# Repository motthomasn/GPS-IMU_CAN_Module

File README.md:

# GPS-IMU_CAN_Module
Teensy 3.2 based controller board designed to collect GPS &amp; IMU data from SkyTraq Venus838LPx and Bosch BNO055 breakout boards and transmit the data via CAN-Bus

This module was built for my CBR250RRi project. The aim was to have a standalone GPS & IMU module which could send high frequency positional data via CAN-Bus to an ECU or datalogger and therefore improve track performance analysis.

The SkyTraq Venus838LPx breakout board allows GPS data acquisition rates up to 50Hz. The BNO055 breakout board was chosen due to the fact that spatial orientation data was calculated internally. However, the spatial orientation (Euler) angles have proved unreliable so a different sensor or calculation method may need to be looked at.

For further details on the CBR250RRi project, refer to the website https://www.cbr250rri.com/.

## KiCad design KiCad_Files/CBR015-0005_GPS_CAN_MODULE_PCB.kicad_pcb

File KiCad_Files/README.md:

This folder contains the KiCad files for the GPS-IMU CAN Module

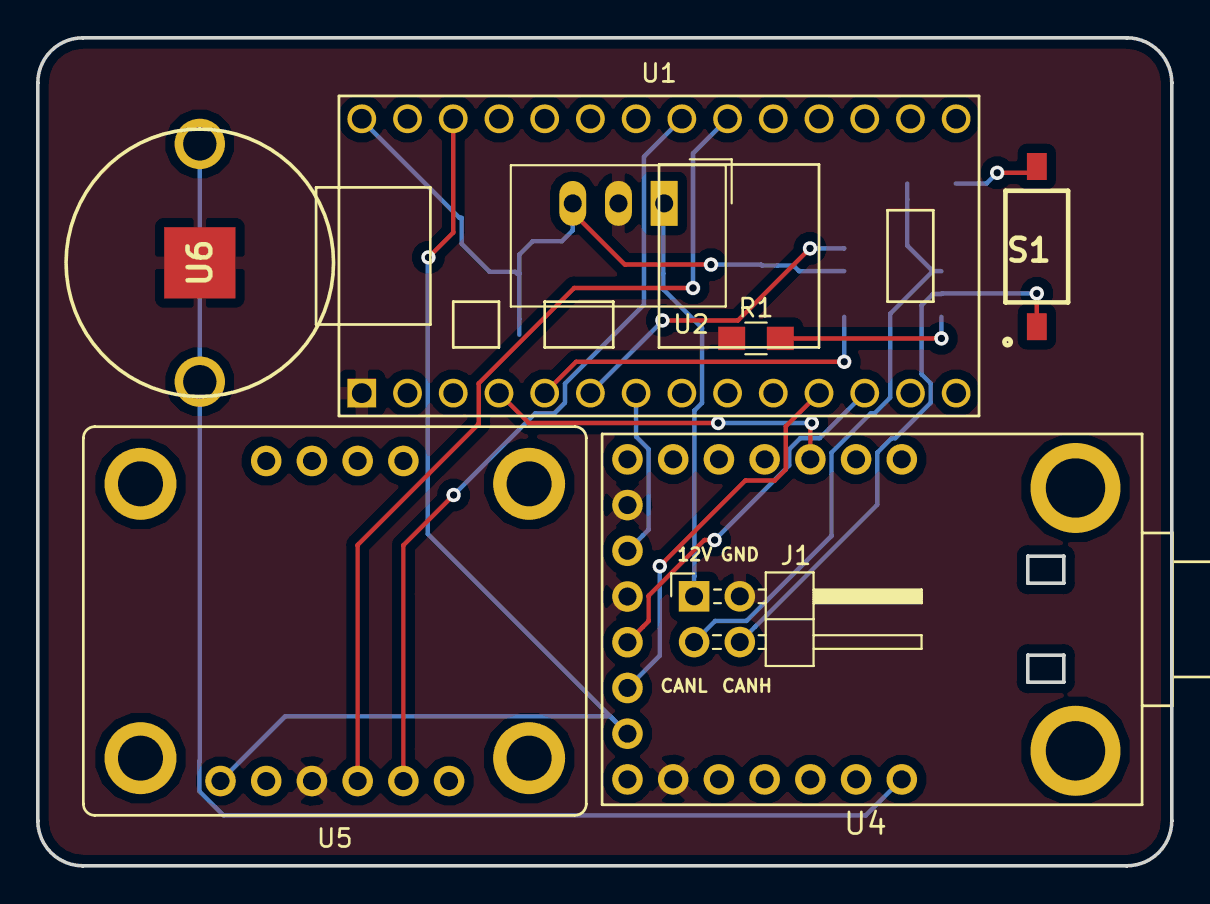
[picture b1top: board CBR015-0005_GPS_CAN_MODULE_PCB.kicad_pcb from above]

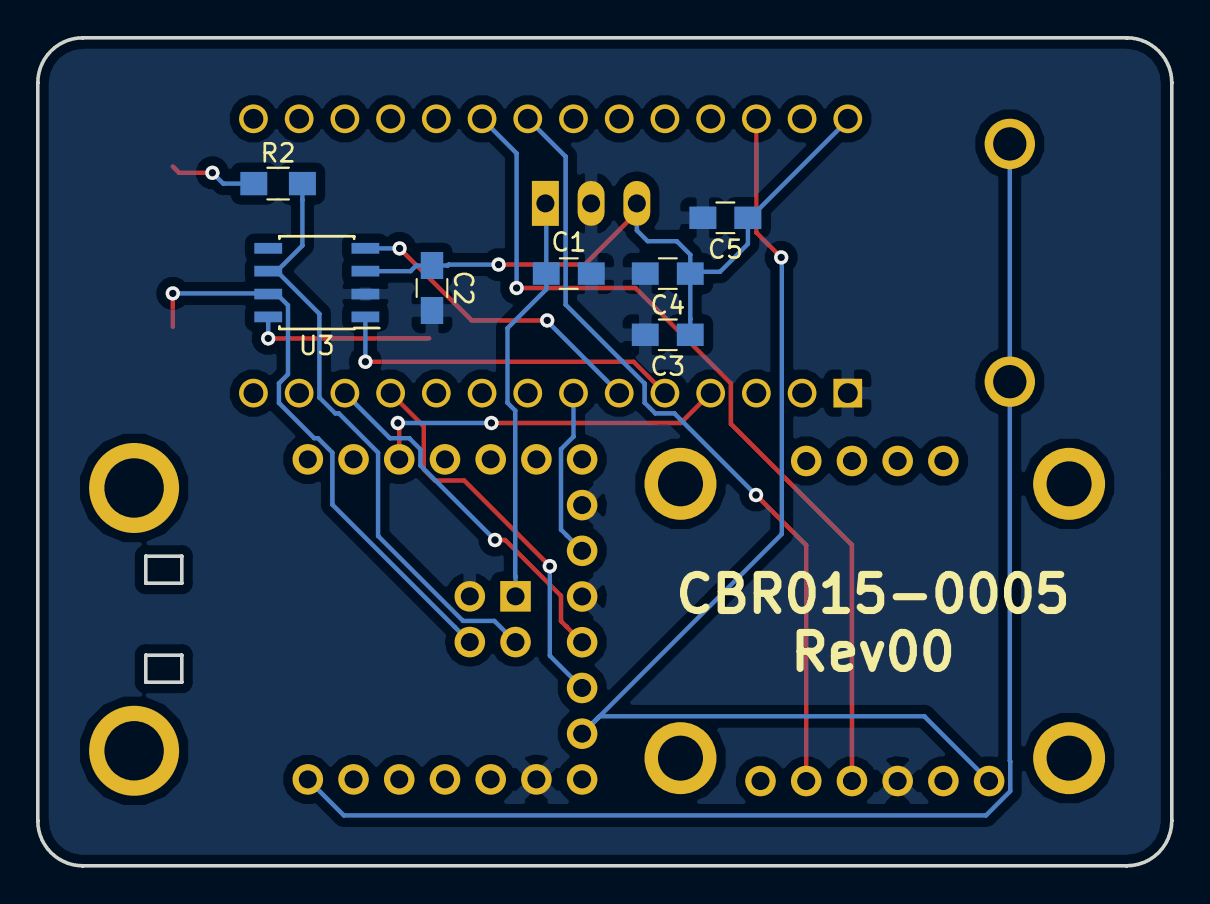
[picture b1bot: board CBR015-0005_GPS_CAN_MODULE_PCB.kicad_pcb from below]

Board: 2 copper layers, 63.0 x 46.0 mm, 15 parts (7 on the bottom side), 17 nets.

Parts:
C1: 22µF; C_0805_HandSoldering
C2: 100nF; C_0805_HandSoldering
C3, C4, C5: 10nF; C_0805_HandSoldering
J1: Conn_01x04_Male; Pin_Header_Angled_2x02_Pitch2.54mm
R1: 18K; R_0805_HandSoldering
R2: 120; R_0805_HandSoldering
S1: IKD0103101
U1: TEENSY_3.2_BASIC
U2: TSR_1-2450; DCDC-Conv_TRACO_TSR-1
U3: MCP2551-I-SN; SOIC-8_3.9x4.9mm_Pitch1.27mm
U4: VENUS838FLPx_BREAKOUT
U5: ADAFRUIT_BNO055; ADAFRUIT_BNO055_BREAKOUT
U6: 3001

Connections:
+3V3: U1.26, U4.15, U5.1
+5V: C2.1, C3.1, C4.1, C5.1, U1.28, U2.3, U3.3
+12V: C1.1, J1.1, U2.1
CANH: J1.4, S1.1, U3.7
CANL: J1.3, R2.2, U3.6
GND: C1.2, C2.2, C3.2, C4.2, C5.2, J1.2, R1.1, U1.1, U2.2, U3.2, U4.2, U4.18, U4.20, U5.3, U6.3
GPS_P1PPS: U1.4, U4.12
GPS_RST: U1.7, U4.19
GPS_RXD0: U1.12, U4.17
GPS_TXD0: U1.11, U4.16
unnamed: R1.2, U3.8
RX_CAN: U1.6, U3.4
SCL: U1.21, U5.5
SDA: U1.20, U5.4
TERML: R2.1, S1.2
TX_CAN: U1.5, U3.1
VBAT: U4.7, U6.1, U6.2

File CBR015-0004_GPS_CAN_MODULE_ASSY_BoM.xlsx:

Designation | Qty | Description | Value | Manufacturer | Part Number | Package | Supplier | Stock No. / Order Code | Notes | Datasheet
U1 | 1 | Teensy 3.2 |  | PJRC | Teensy 3.2 | PDIP
 | 2 | Teensy Pin Header | 14-way, 2.54mm
 | 2 | Teensy Connector Socket | 14-way, 2.54mm
U2 | 1 | Board Power Regulator | 5V, 1A | Traco Power | TSR 1-2450 | SIP 3 | RS | 666-4379 |  | https://www.tracopower.com/products/tsr1.pdf
U3 | 1 | CAN Transceiver |  | Microchip | MCP2551-I/SN | SOIC 8 | RS | 738-6036 |  | http://ww1.microchip.com/downloads/en/DeviceDoc/21667E.pdf
U4 | 1 | GPS Breakout |  |  | VENUS838FLPx |  |  |  |  | https://www.skytraq.com.tw/products/Venus838FLPx_PB_v1.pdf
 | 2 | GPS Pin Header A | 7-way, 2.54mm
 | 1 | GPS Pin Header B | 6-way, 2.54mm
 | 2 | GPS Connector Socket A | 7-way, 2.54mm
 | 1 | GPS Connector Socket B | 6-way, 2.54mm
 | 2 | GPS Standoff | M3 x 11
 | 4 | GPS Standoff Screw | M3x6
U5 | 1 | IMU |  | Adafruit | BNO055 Breakout | PDIP
 | 1 | IMU Pin Header A | 6-way, 2.54mm
 | 1 | IMU Pin Header B | 4-way, 2.54mm
 | 1 | IMU Connector Socket A | 6-way, 2.54mm
 | 1 | IMU Connector Socket B | 4-way, 2.54mm
 | 4 | IMU Standoff | M2 x 11
 | 8 | IMU Standoff Screw | M2
U6 | 1 | Coin Battery Holder |  | Keystone | 3001 |  | RS | 219-7948 |  | https://www.keyelco.com/product.cfm/product_id/778
C1 | 1 | Power Reg Smoothing Cap | 22µF | Murata | GRM219B30G226ME66D | 0805 | RS | 798-4624
C2 | 1 | CAN Transciever Input Smoothing Cap | 100nF | AVX | 08055C104KAT2A | 0805 | RS | 464-6688
C3 | 1 | Power Reg Output Smoothing Cap | 10nF | AVX | 08055C103KAT2A | 0805 | RS | 464-6672
C4 | 1 | Power Reg Output Smoothing Cap | 10nF | AVX | 08055C103KAT2A | 0805 | RS | 464-6672
C5 | 1 | Power Reg Output Smoothing Cap | 10nF | AVX | 08055C103KAT2A | 0805 | RS | 464-6672
R1 | 1 | CAN Transciever Reset Resistor | 18K | TE Connectivity | CRG0805F18K | 0805 | RS | 223-0590
R2 | 1 | CAN Termination Resistor | 120 | Panasonic | ERJP06F1200V | 0805 | RS | 721-7674
S1 | 1 | CAN Termination Jumper | Single SPST | APEM | IKD0103101 |  | RS | 877-2233 |  | https://www.apem.com/int/ikd-series-168.html
P1 | 1 | Board Connector | 4 Way, 2 Row, Right Angle Pin Header

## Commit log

2023-06-13 Update main.cpp to v2.2
    CAN message IDs updated to match CBR250RRi CAN config v3.0
